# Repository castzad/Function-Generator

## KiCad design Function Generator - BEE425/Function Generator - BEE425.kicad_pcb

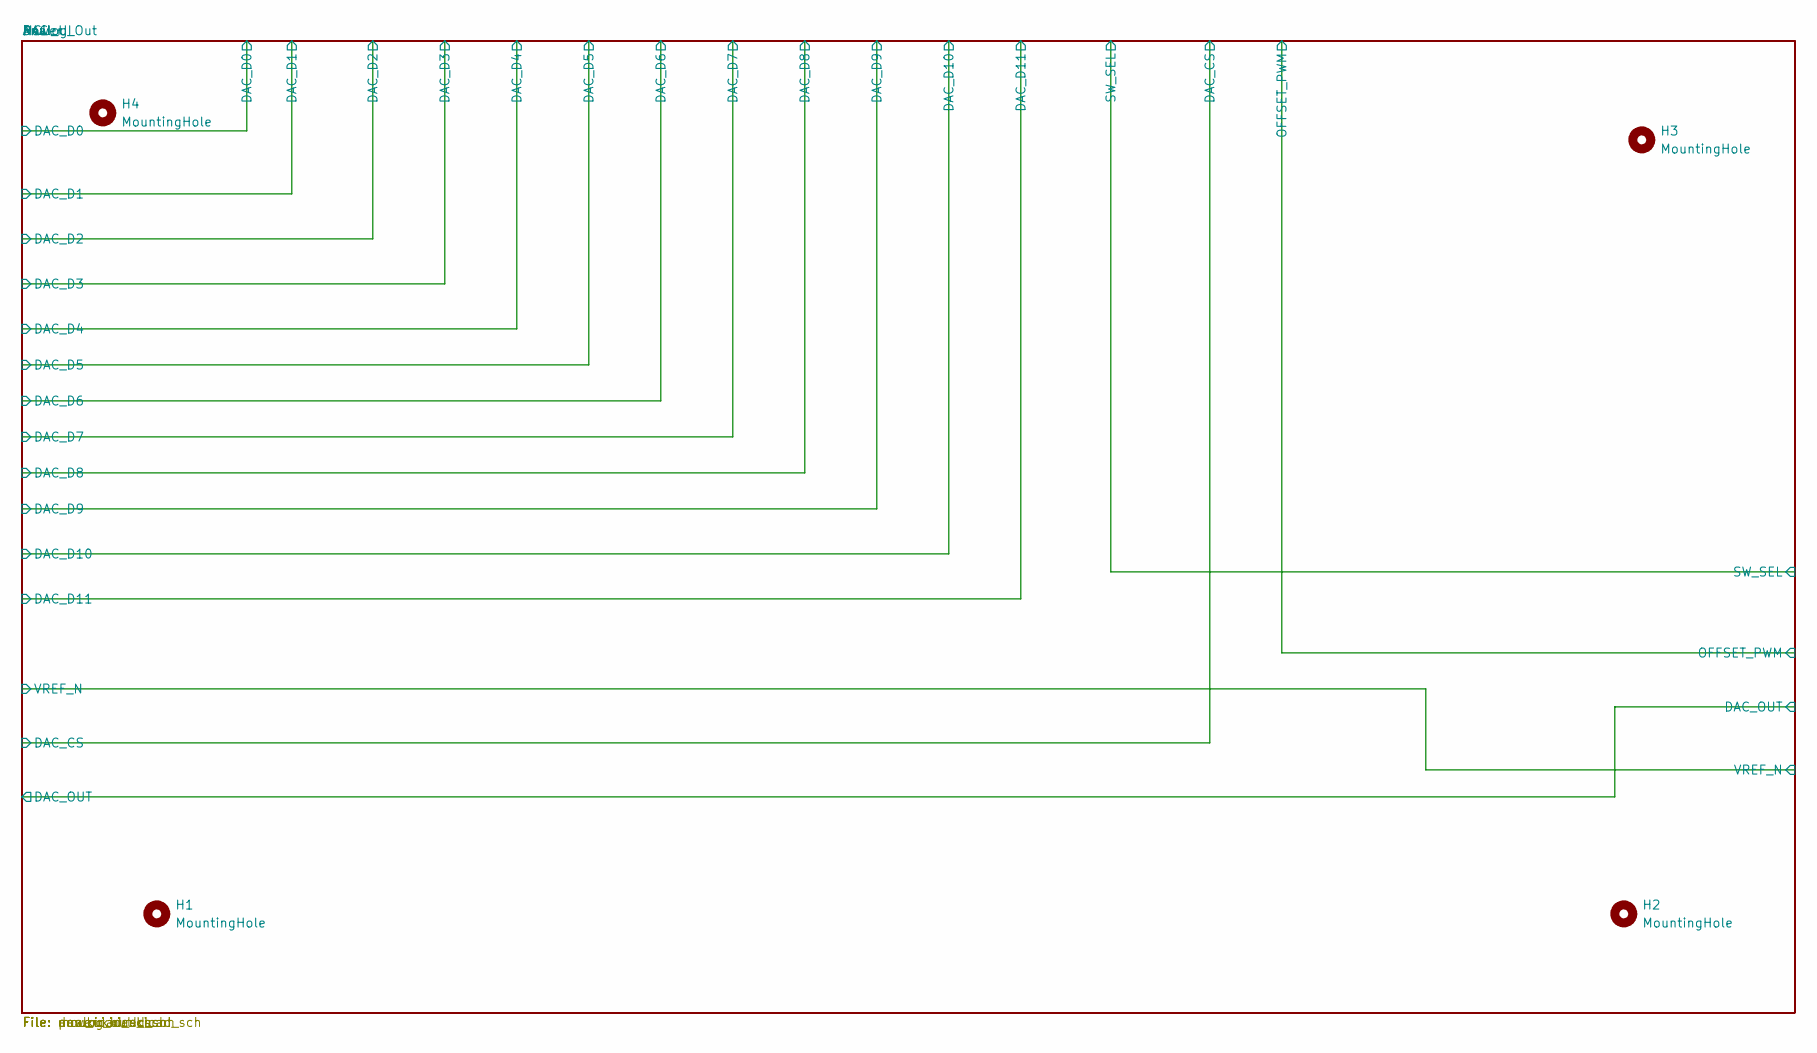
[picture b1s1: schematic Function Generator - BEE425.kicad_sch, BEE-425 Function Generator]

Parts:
H1, H2, H3, H4: MountingHole; MountingHole_3.2mm_M3

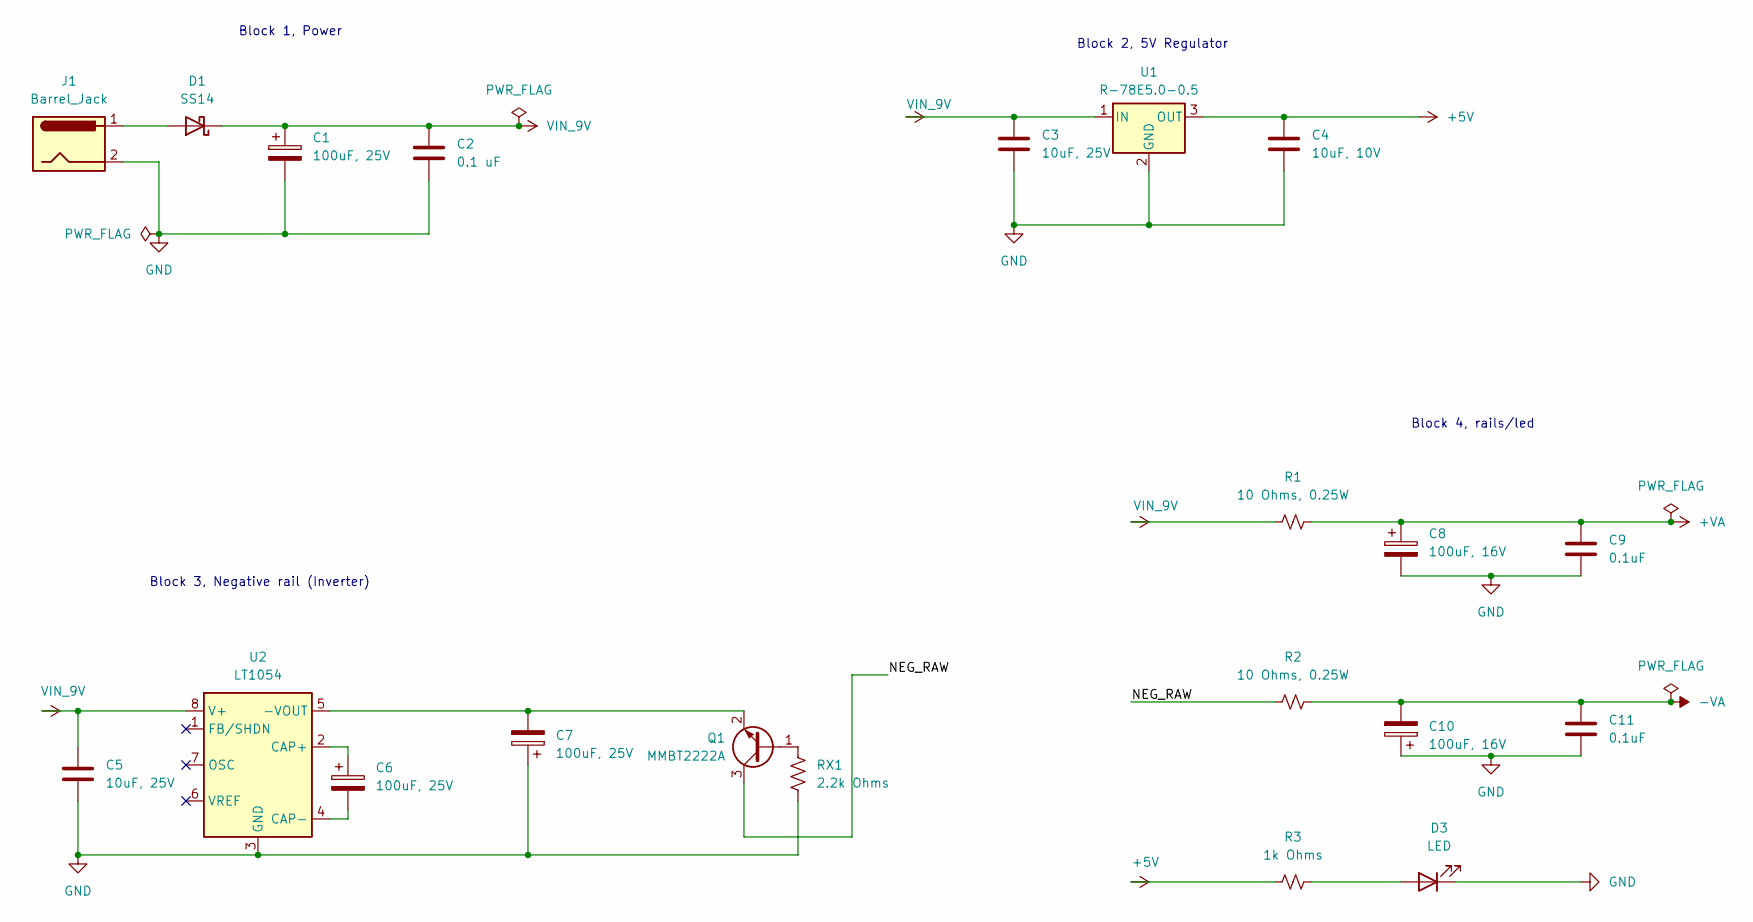
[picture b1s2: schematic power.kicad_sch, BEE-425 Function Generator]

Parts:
C1, C6, C7: 100uF, 25V; CP_Radial_D6.3mm_P2.50mm
C2: 0.1 uF; C_0805_2012Metric_Pad1.18x1.45mm_HandSolder
C3, C5: 10uF, 25V; C_1206_3216Metric_Pad1.33x1.80mm_HandSolder
C4: 10uF, 10V; C_1206_3216Metric_Pad1.33x1.80mm_HandSolder
C8, C10: 100uF, 16V; CP_Radial_D6.3mm_P2.50mm
C9, C11: 0.1uF; C_0805_2012Metric_Pad1.18x1.45mm_HandSolder
D1: SS14; D_SMA
D3: LED; LED_0805_2012Metric_Pad1.15x1.40mm_HandSolder
J1: Barrel_Jack; BarrelJack_Horizontal
Q1: MMBT2222A; SOT-23
R1, R2: 10 Ohms, 0.25W; R_0805_2012Metric_Pad1.20x1.40mm_HandSolder
R3: 1k Ohms; R_0805_2012Metric_Pad1.20x1.40mm_HandSolder
RX1: 2.2k Ohms; R_0805_2012Metric_Pad1.20x1.40mm_HandSolder
U1: R-78E5.0-0.5; Converter_DCDC_RECOM_R-78E-0.5_THT
U2: LT1054; SOIC-8_3.9x4.9mm_P1.27mm

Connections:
+5V: C4.1, R3.2, U1.3 (OUT); also elsewhere on the board
+VA: C8.1, C9.1, R1.2; also elsewhere on the board
-VA: C10.2, C11.1, R2.2; also elsewhere on the board
/Power/NEG_RAW: Q1.3 (C), R2.1
GND: C1.2, C2.2, C3.2, C4.2, C5.2, C7.1, C8.2, C9.2, C10.1, C11.2, D3.1 (K), J1.2, RX1.2, U1.2 (GND), U2.3 (GND); also elsewhere on the board
unnamed: D1.2 (A), J1.1
unnamed: D3.2 (A), R3.1
unnamed: Q1.1 (B), RX1.1
unnamed: C7.2, Q1.2 (E), U2.5 (-VOUT)
unnamed: C6.1, U2.2 (CAP+)
unnamed: C6.2, U2.4 (CAP-)
VIN_9V: C1.1, C2.1, C3.1, C5.1, D1.1 (K), R1.1, U1.1 (IN), U2.8 (V+)

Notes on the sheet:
Block 2, 5V Regulator
Block 1, Power
Block 3, Negative rail (Inverter)
Block 4, rails/led

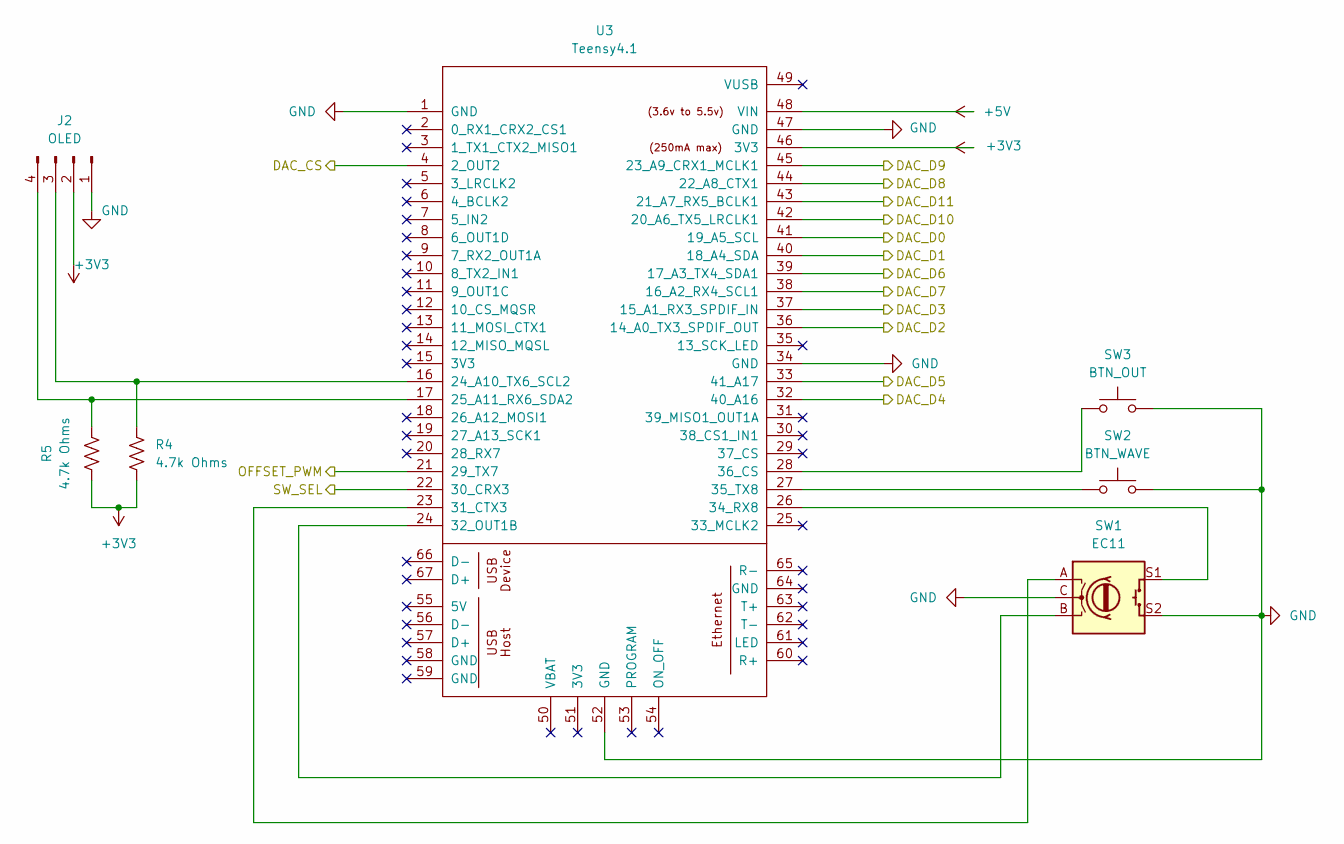
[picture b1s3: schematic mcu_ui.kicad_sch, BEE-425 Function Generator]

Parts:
J2: OLED; PinSocket_1x04_P2.54mm_Vertical
R4, R5: 4.7k Ohms; R_0805_2012Metric_Pad1.20x1.40mm_HandSolder
SW1: EC11; RotaryEncoder_Alps_EC11E-Switch_Vertical_H20mm
SW2: BTN_WAVE; SW_PUSH_6mm
SW3: BTN_OUT; SW_PUSH_6mm
U3: Teensy4.1; Teensy41

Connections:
+3V3: J2.2, R4.1, R5.1, U3.46 (3V3); also elsewhere on the board
+5V: U3.48 (VIN); also elsewhere on the board
/Analog_Out/OFFSET_PWM: U3.21 (29_TX7); also elsewhere on the board
/Analog_Out/SW_SEL: U3.22 (30_CRX3); also elsewhere on the board
/DAC/DAC_CS: U3.4 (2_OUT2); also elsewhere on the board
/DAC/DAC_D0: U3.41 (19_A5_SCL); also elsewhere on the board
/DAC/DAC_D1: U3.40 (18_A4_SDA); also elsewhere on the board
/DAC/DAC_D2: U3.36 (14_A0_TX3_SPDIF_OUT); also elsewhere on the board
/DAC/DAC_D3: U3.37 (15_A1_RX3_SPDIF_IN); also elsewhere on the board
/DAC/DAC_D4: U3.32 (40_A16); also elsewhere on the board
/DAC/DAC_D5: U3.33 (41_A17); also elsewhere on the board
/DAC/DAC_D6: U3.39 (17_A3_TX4_SDA1); also elsewhere on the board
/DAC/DAC_D7: U3.38 (16_A2_RX4_SCL1); also elsewhere on the board
/DAC/DAC_D8: U3.44 (22_A8_CTX1); also elsewhere on the board
/DAC/DAC_D9: U3.45 (23_A9_CRX1_MCLK1); also elsewhere on the board
/DAC/DAC_D10: U3.42 (20_A6_TX5_LRCLK1); also elsewhere on the board
/DAC/DAC_D11: U3.43 (21_A7_RX5_BCLK1); also elsewhere on the board
GND: J2.1, SW1.C, SW1.S2, SW2.2, SW3.2, U3.1 (GND), U3.34 (GND), U3.47 (GND), U3.52 (GND); also elsewhere on the board
unnamed: J2.3, R4.2, U3.16 (24_A10_TX6_SCL2)
unnamed: J2.4, R5.2, U3.17 (25_A11_RX6_SDA2)
unnamed: SW1.A, U3.23 (31_CTX3)
unnamed: SW1.B, U3.24 (32_OUT1B)
unnamed: SW1.S1, U3.26 (34_RX8)
unnamed: SW2.1, U3.27 (35_TX8)
unnamed: SW3.1, U3.28 (36_CS)

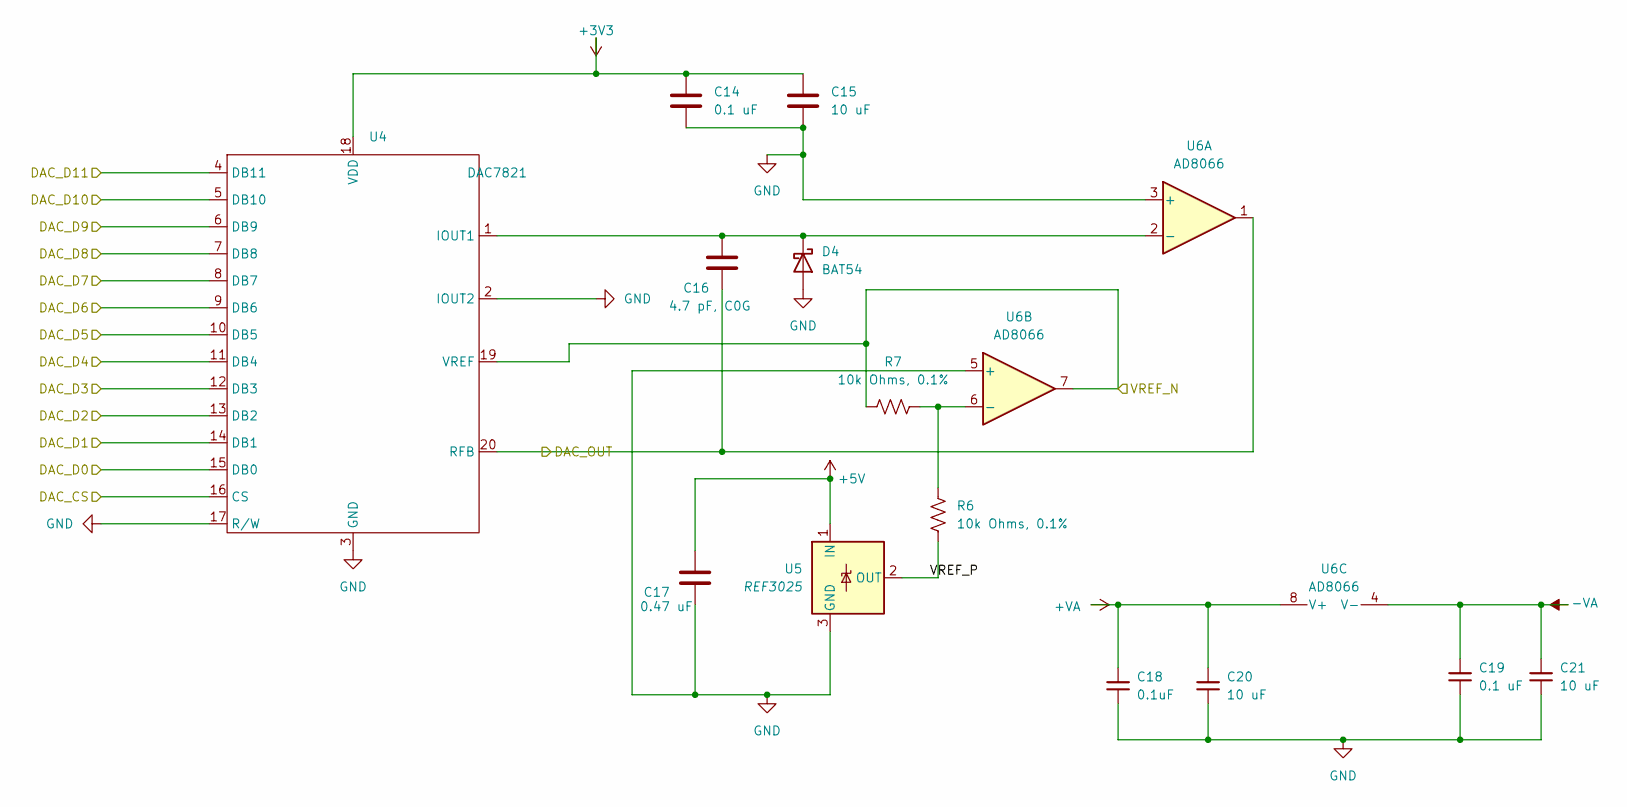
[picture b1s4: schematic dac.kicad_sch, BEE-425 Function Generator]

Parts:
C14, C19: 0.1 uF; C_0805_2012Metric_Pad1.18x1.45mm_HandSolder
C15, C20, C21: 10 uF; C_1206_3216Metric_Pad1.33x1.80mm_HandSolder
C16: 4.7 pF, C0G; C_0805_2012Metric_Pad1.18x1.45mm_HandSolder
C17: 0.47 uF; C_0805_2012Metric_Pad1.18x1.45mm_HandSolder
C18: 0.1uF; C_0805_2012Metric_Pad1.18x1.45mm_HandSolder
D4: BAT54; D_SOD-123
R6, R7: 10k Ohms, 0.1%; R_0805_2012Metric_Pad1.20x1.40mm_HandSolder
U4: DAC7821; TSSOP-20_4.4x6.5mm_P0.65mm
U5: REF3025; SOT-23
U6: AD8066; SOIC-8_3.9x4.9mm_P1.27mm

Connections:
+3V3: C14.1, C15.1, U4.18 (VDD); also elsewhere on the board
+5V: C17.1, U5.1 (IN); also elsewhere on the board
+VA: C18.1, C20.1, U6.8 (V+); also elsewhere on the board
-VA: C19.1, C21.1, U6.4 (V-); also elsewhere on the board
/Analog_Out/DAC_OUT: C16.2, U4.20 (RFB), U6.1; also elsewhere on the board
/Analog_Out/VREF_N: R7.1, U4.19 (VREF), U6.7; also elsewhere on the board
/DAC/DAC_CS: U4.16 (CS); also elsewhere on the board
/DAC/DAC_D0: U4.15 (DB0); also elsewhere on the board
/DAC/DAC_D1: U4.14 (DB1); also elsewhere on the board
/DAC/DAC_D2: U4.13 (DB2); also elsewhere on the board
/DAC/DAC_D3: U4.12 (DB3); also elsewhere on the board
/DAC/DAC_D4: U4.11 (DB4); also elsewhere on the board
/DAC/DAC_D5: U4.10 (DB5); also elsewhere on the board
/DAC/DAC_D6: U4.9 (DB6); also elsewhere on the board
/DAC/DAC_D7: U4.8 (DB7); also elsewhere on the board
/DAC/DAC_D8: U4.7 (DB8); also elsewhere on the board
/DAC/DAC_D9: U4.6 (DB9); also elsewhere on the board
/DAC/DAC_D10: U4.5 (DB10); also elsewhere on the board
/DAC/DAC_D11: U4.4 (DB11); also elsewhere on the board
/DAC/VREF_P: R6.2, U5.2 (OUT)
GND: C14.2, C15.2, C17.2, C18.2, C19.2, C20.2, C21.2, D4.2 (A), U4.2 (IOUT2), U4.3 (GND), U4.17 (R/W), U5.3 (GND), U6.3 (+), U6.5 (+); also elsewhere on the board
unnamed: C16.1, D4.1 (K), U4.1 (IOUT1), U6.2 (-)
unnamed: R6.1, R7.2, U6.6 (-)

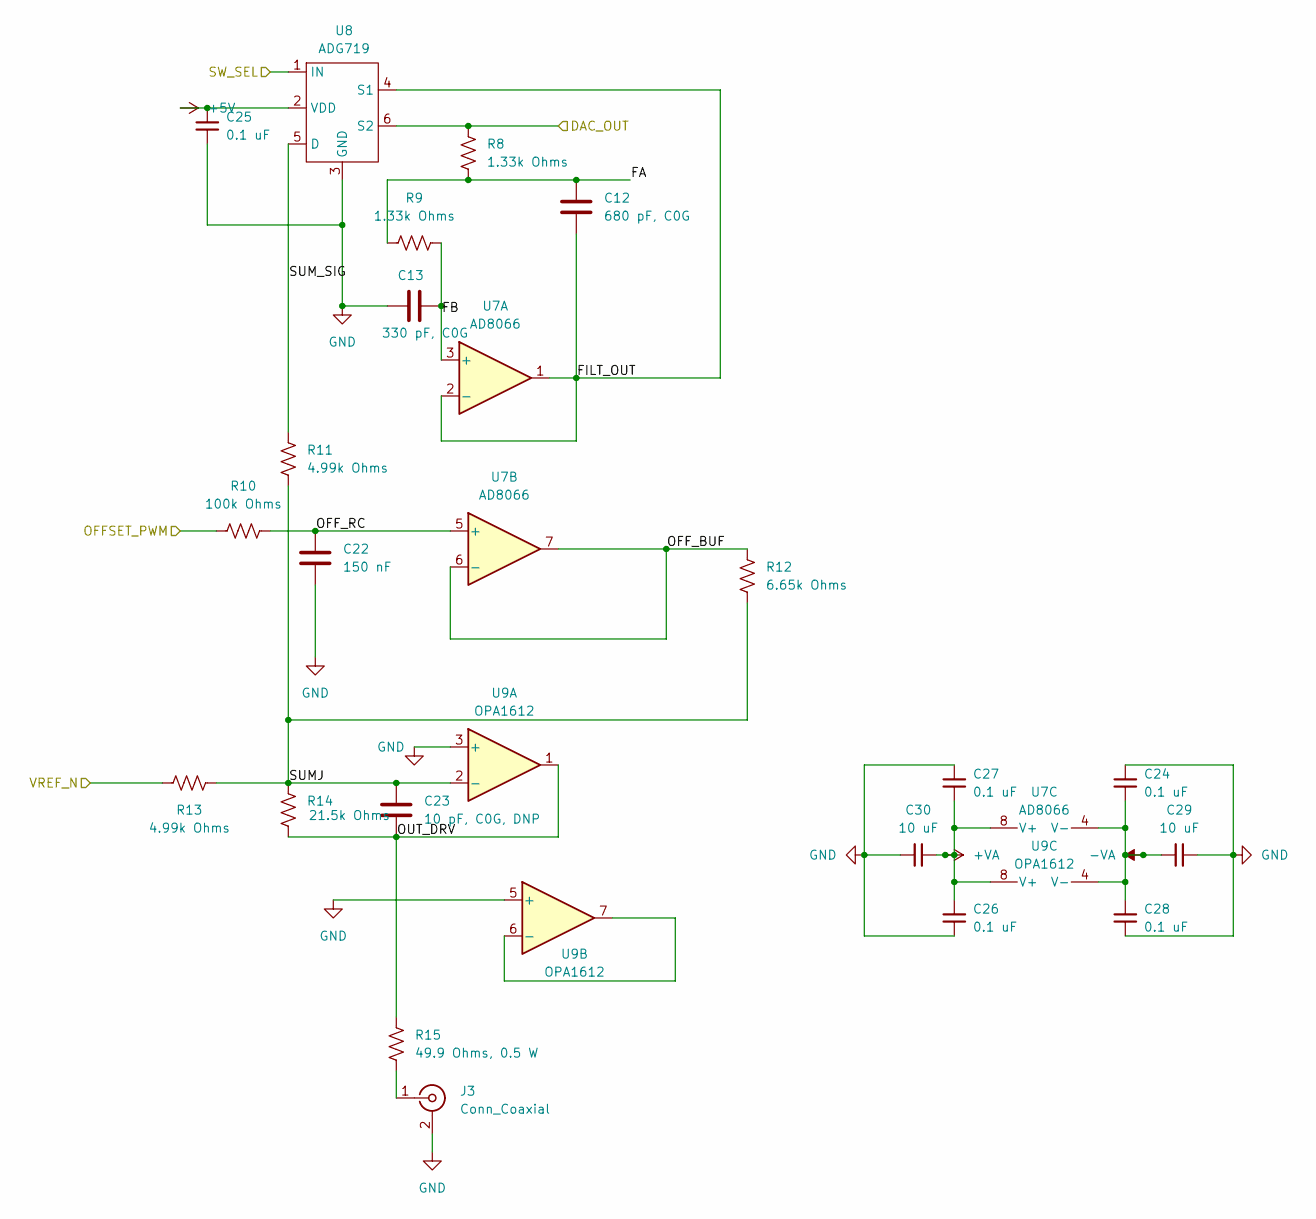
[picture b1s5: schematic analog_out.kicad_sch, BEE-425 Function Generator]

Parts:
C12: 680 pF, C0G; C_0805_2012Metric_Pad1.18x1.45mm_HandSolder
C13: 330 pF, C0G; C_0805_2012Metric_Pad1.18x1.45mm_HandSolder
C22: 150 nF; C_0805_2012Metric_Pad1.18x1.45mm_HandSolder
C23: 10 pF, C0G, DNP; C_0805_2012Metric_Pad1.18x1.45mm_HandSolder
C24, C25, C26, C27, C28: 0.1 uF; C_0805_2012Metric_Pad1.18x1.45mm_HandSolder
C29, C30: 10 uF; C_1206_3216Metric_Pad1.33x1.80mm_HandSolder
J3: Conn_Coaxial; BNC_Amphenol_B6252HB-NPP3G-50_Horizontal
R8, R9: 1.33k Ohms; R_0805_2012Metric_Pad1.20x1.40mm_HandSolder
R10: 100k Ohms; R_0805_2012Metric_Pad1.20x1.40mm_HandSolder
R11, R13: 4.99k Ohms; R_0805_2012Metric_Pad1.20x1.40mm_HandSolder
R12: 6.65k Ohms; R_0805_2012Metric_Pad1.20x1.40mm_HandSolder
R14: 21.5k Ohms; R_0805_2012Metric_Pad1.20x1.40mm_HandSolder
R15: 49.9 Ohms, 0.5 W; R_Axial_DIN0207_L6.3mm_D2.5mm_P10.16mm_Horizontal
U7: AD8066; SOIC-8_3.9x4.9mm_P1.27mm
U8: ADG719; SOT-23-6
U9: OPA1612; SOIC-8_3.9x4.9mm_P1.27mm

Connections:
+5V: C25.1, U8.2 (VDD); also elsewhere on the board
+VA: C26.2, C27.2, C30.2, U7.8 (V+), U9.8 (V+); also elsewhere on the board
-VA: C24.2, C28.1, C29.1, U7.4 (V-), U9.4 (V-); also elsewhere on the board
/Analog_Out/DAC_OUT: R8.2, U8.6 (S2); also elsewhere on the board
/Analog_Out/FA: C12.1, R8.1, R9.1
/Analog_Out/FB: C13.2, R9.2, U7.3 (+)
/Analog_Out/FILT_OUT: C12.2, U7.1, U7.2 (-), U8.4 (S1)
/Analog_Out/OFFSET_PWM: R10.1; also elsewhere on the board
/Analog_Out/OFF_BUF: R12.1, U7.6 (-), U7.7
/Analog_Out/OFF_RC: C22.1, R10.2, U7.5 (+)
/Analog_Out/OUT_DRV: C23.1, R14.2, R15.1, U9.1
/Analog_Out/SUMJ: C23.2, R11.1, R12.2, R13.2, R14.1, U9.2 (-)
/Analog_Out/SUM_SIG: R11.2, U8.5 (D)
/Analog_Out/SW_SEL: U8.1 (IN); also elsewhere on the board
/Analog_Out/VREF_N: R13.1; also elsewhere on the board
GND: C13.1, C22.2, C24.1, C25.2, C26.1, C27.1, C28.2, C29.2, C30.1, J3.2 (Ext), U8.3 (GND), U9.3 (+), U9.5 (+); also elsewhere on the board
unnamed: J3.1 (In), R15.2
unnamed: U9.6 (-), U9.7

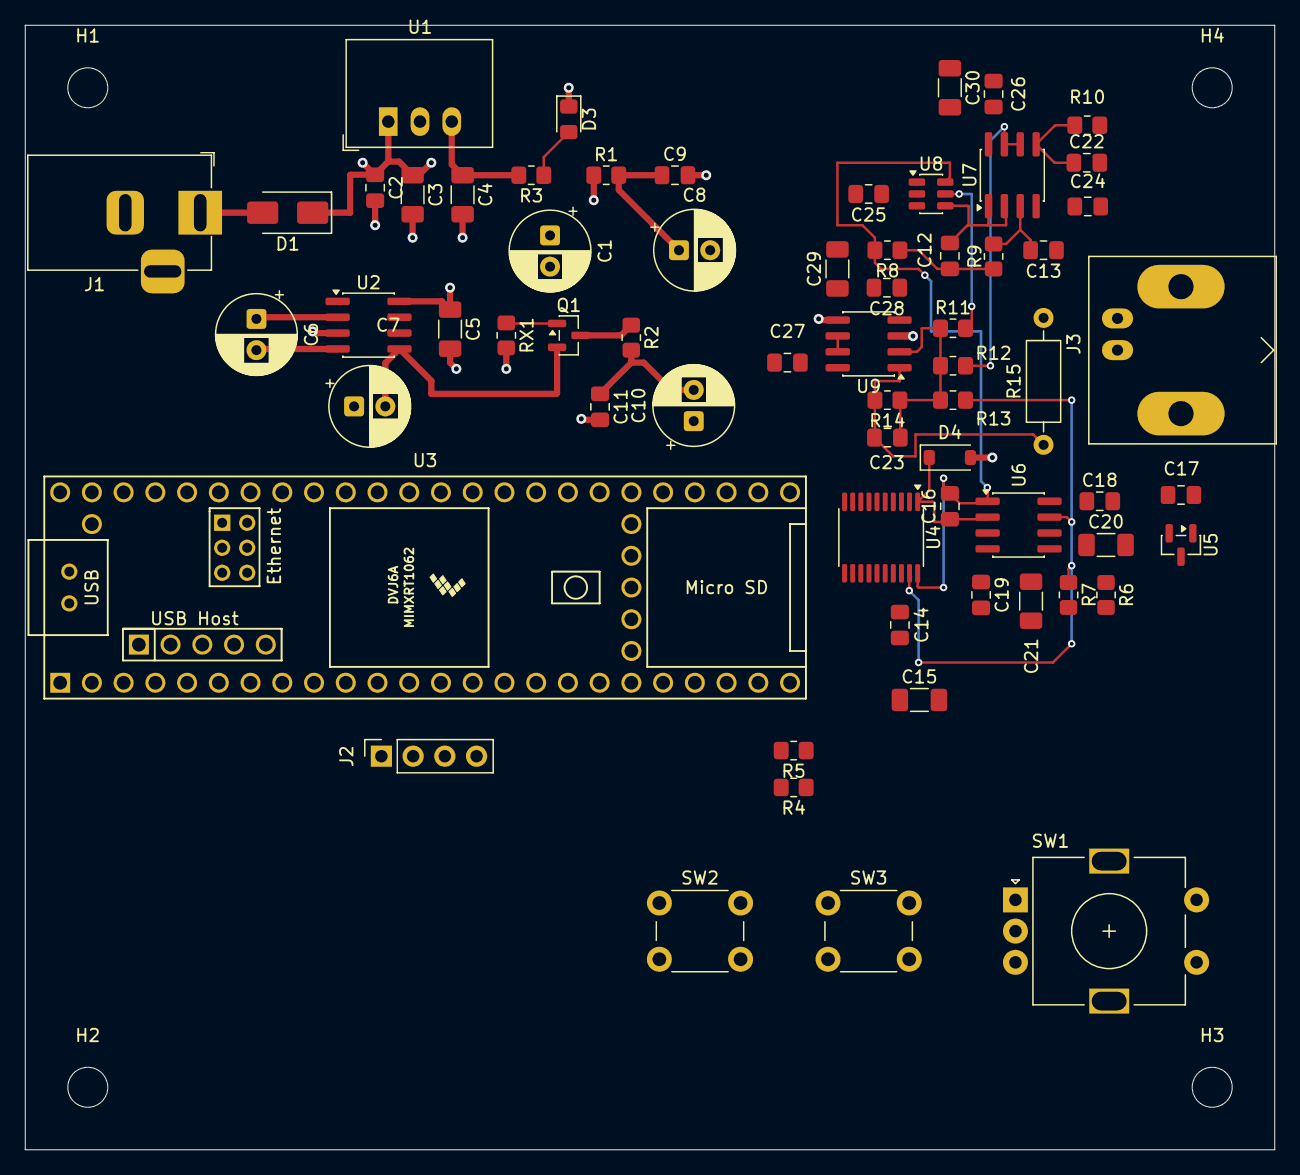
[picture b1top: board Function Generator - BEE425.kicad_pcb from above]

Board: 4 copper layers, 100.0 x 90.0 mm, 69 parts (0 on the bottom side), 50 nets.
